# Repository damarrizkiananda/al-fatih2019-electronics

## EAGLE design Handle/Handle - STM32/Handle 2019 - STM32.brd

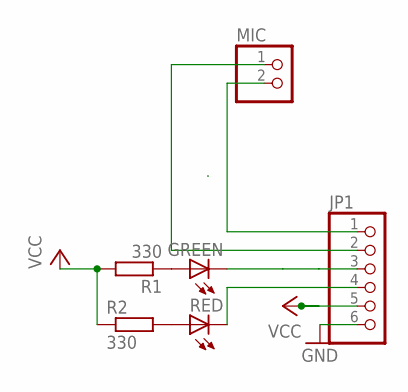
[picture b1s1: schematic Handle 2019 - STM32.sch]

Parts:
GREEN: LED5MM
JP1: PINHD-1X6; 1X06
MIC: PINHD-1X2; 1X02
R1, R2: 330; M1206
RED: LED5MM

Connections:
GND: JP1.6
unnamed: GREEN.K (C), JP1.3
unnamed: JP1.2, MIC.1
unnamed: JP1.1, MIC.2
unnamed: GREEN.A, R1.1
unnamed: R2.2, RED.A
unnamed: JP1.4, RED.K (C)
VCC: JP1.5, R1.2, R2.1

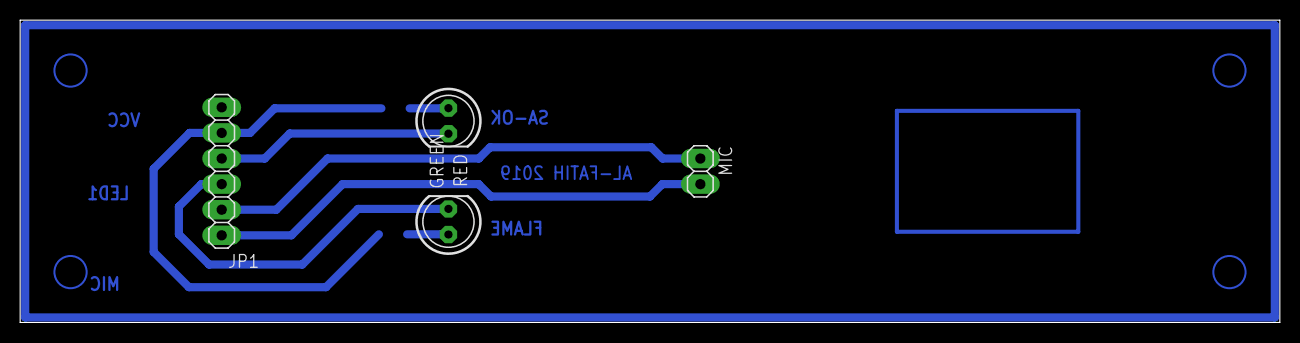
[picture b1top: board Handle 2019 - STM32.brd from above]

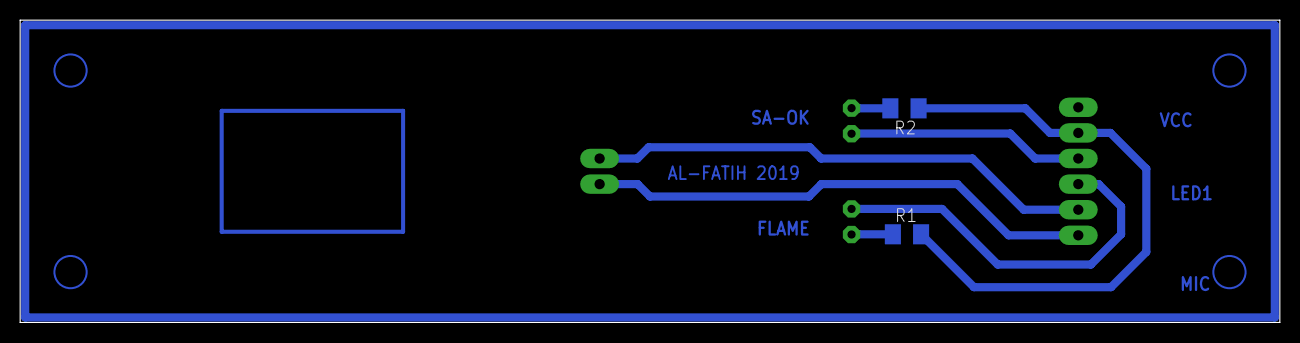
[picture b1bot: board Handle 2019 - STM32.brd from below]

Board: 2 copper layers, 125.0 x 30.0 mm, 6 parts (2 on the bottom side), 7 nets.

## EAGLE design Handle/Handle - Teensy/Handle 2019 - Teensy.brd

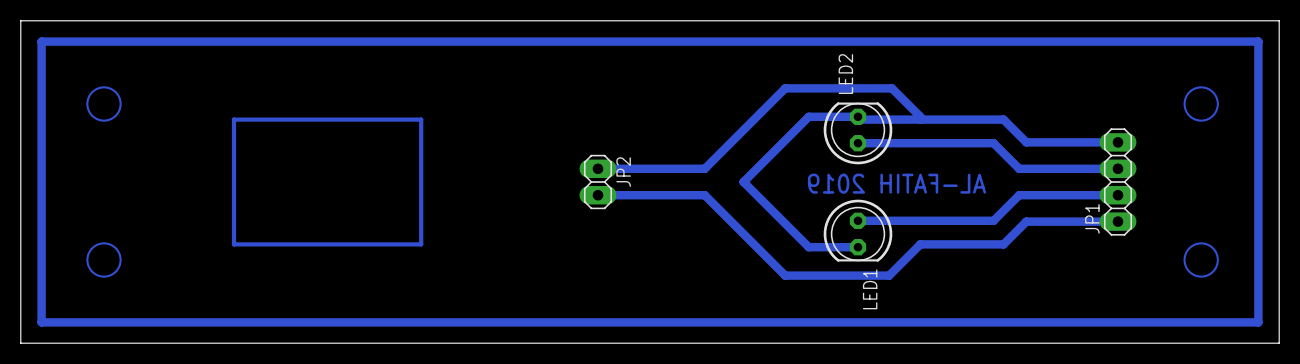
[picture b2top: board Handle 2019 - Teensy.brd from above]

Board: 2 copper layers, 121.0 x 31.0 mm, 4 parts (0 on the bottom side), 4 nets.

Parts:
JP1: 1X04
JP2: 1X02
LED1, LED2: LED5MM

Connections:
GND: JP1.4, JP2.1, LED1.K, LED2.K
LED1: JP1.2, LED1.A
LED2: JP1.3, LED2.A
unnamed: JP1.1, JP2.2

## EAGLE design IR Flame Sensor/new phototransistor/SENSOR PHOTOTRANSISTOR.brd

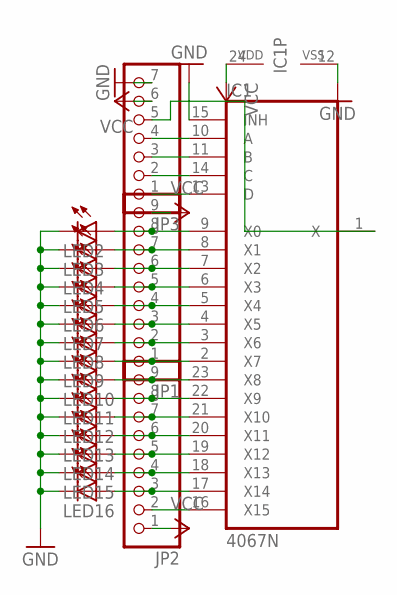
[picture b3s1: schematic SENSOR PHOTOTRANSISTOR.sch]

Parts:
IC1: 4067N; DIL24-6
JP1, JP2: PINHD-1X9; 1X09
JP3: PINHD-1X7; 1X07
LED2, LED3, LED4, LED5, LED6, LED7, LED8, LED9, LED10, LED11, LED12, LED13, LED14, LED15, LED16: LED5MM

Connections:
GND: IC1.12 (VSS), IC1.15 (INH), JP3.7, LED2.K (C), LED3.K (C), LED4.K (C), LED5.K (C), LED6.K (C), LED7.K (C), LED8.K (C), LED9.K (C), LED10.K (C), LED11.K (C), LED12.K (C), LED13.K (C), LED14.K (C), LED15.K (C), LED16.K (C)
unnamed: IC1.9 (X0), JP1.8, LED2.A
unnamed: IC1.8 (X1), JP1.7, LED3.A
unnamed: IC1.7 (X2), JP1.6, LED4.A
unnamed: IC1.6 (X3), JP1.5, LED5.A
unnamed: IC1.5 (X4), JP1.4, LED6.A
unnamed: IC1.4 (X5), JP1.3, LED7.A
unnamed: IC1.3 (X6), JP1.2, LED8.A
unnamed: IC1.2 (X7), JP1.1, LED9.A
unnamed: IC1.23 (X8), JP2.9, LED10.A
unnamed: IC1.22 (X9), JP2.8, LED11.A
unnamed: IC1.21 (X10), JP2.7, LED12.A
unnamed: IC1.20 (X11), JP2.6, LED13.A
unnamed: IC1.19 (X12), JP2.5, LED14.A
unnamed: IC1.18 (X13), JP2.4, LED15.A
unnamed: IC1.17 (X14), JP2.3, LED16.A
unnamed: IC1.16 (X15), JP2.2
unnamed: IC1.13 (D), JP3.1
unnamed: IC1.14 (C), JP3.2
unnamed: IC1.11 (B), JP3.3
unnamed: IC1.10 (A), JP3.4
unnamed: IC1.1 (X), JP3.5
VCC: IC1.24 (VDD), JP1.9, JP2.1, JP3.6

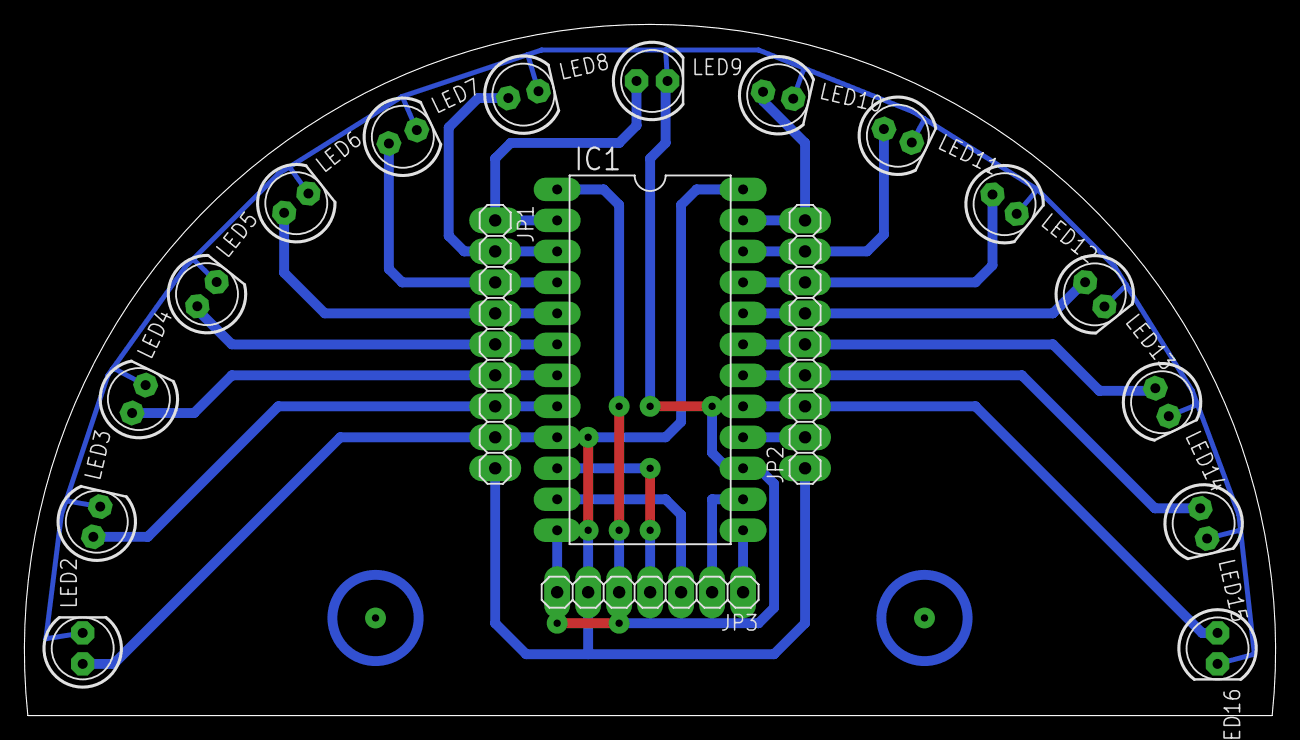
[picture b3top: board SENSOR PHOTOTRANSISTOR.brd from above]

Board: 2 copper layers, 102.6 x 56.7 mm, 19 parts (0 on the bottom side), 23 nets.

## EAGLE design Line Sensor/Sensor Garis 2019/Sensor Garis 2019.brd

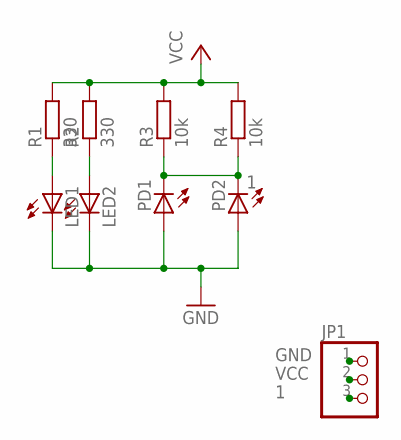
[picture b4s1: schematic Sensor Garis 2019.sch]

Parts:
JP1: PINHD-1X3; 1X03
LED1, LED2: LED3MM
PD1, PD2: LED3MM
R1, R2: 330; M0805
R3, R4: 10k; M0805

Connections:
1: JP1.3, PD1.K (C), PD2.K (C), R3.1, R4.1
GND: JP1.1, LED1.K (C), LED2.K (C), PD1.A, PD2.A
unnamed: LED2.A, R2.1
unnamed: LED1.A, R1.1
VCC: JP1.2, R1.2, R2.2, R3.2, R4.2

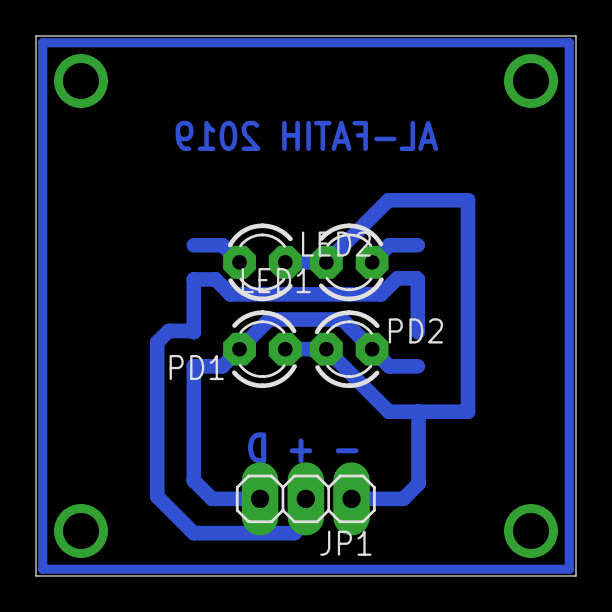
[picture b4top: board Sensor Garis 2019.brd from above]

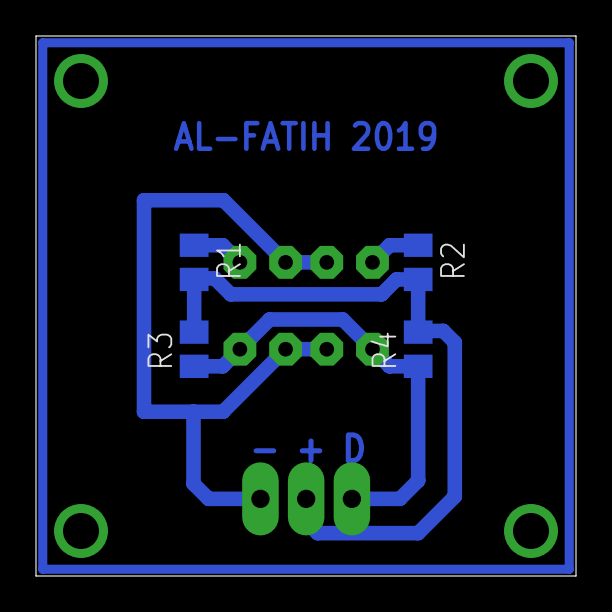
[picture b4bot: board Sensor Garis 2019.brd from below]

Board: 2 copper layers, 30.0 x 30.0 mm, 9 parts (4 on the bottom side), 5 nets.

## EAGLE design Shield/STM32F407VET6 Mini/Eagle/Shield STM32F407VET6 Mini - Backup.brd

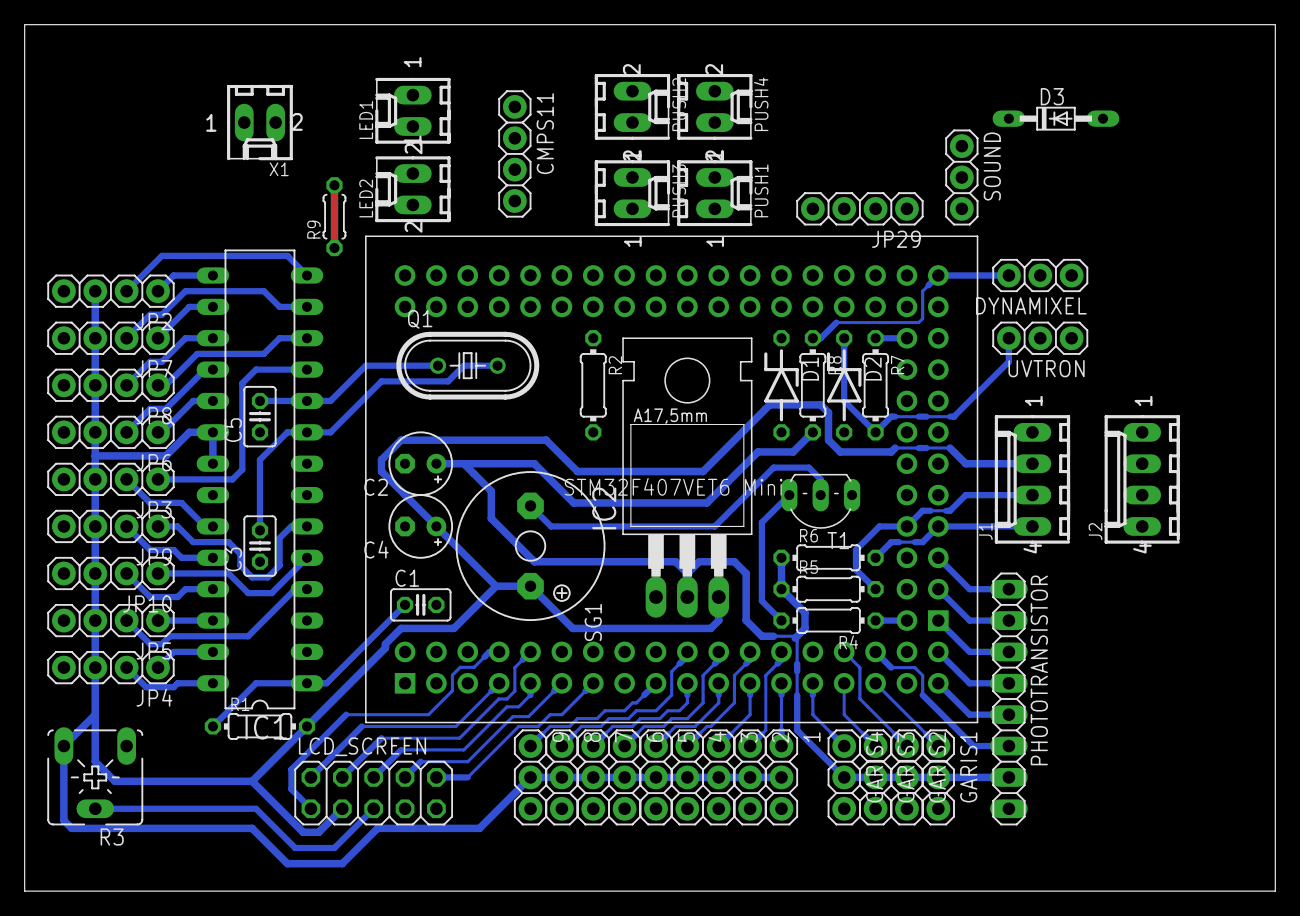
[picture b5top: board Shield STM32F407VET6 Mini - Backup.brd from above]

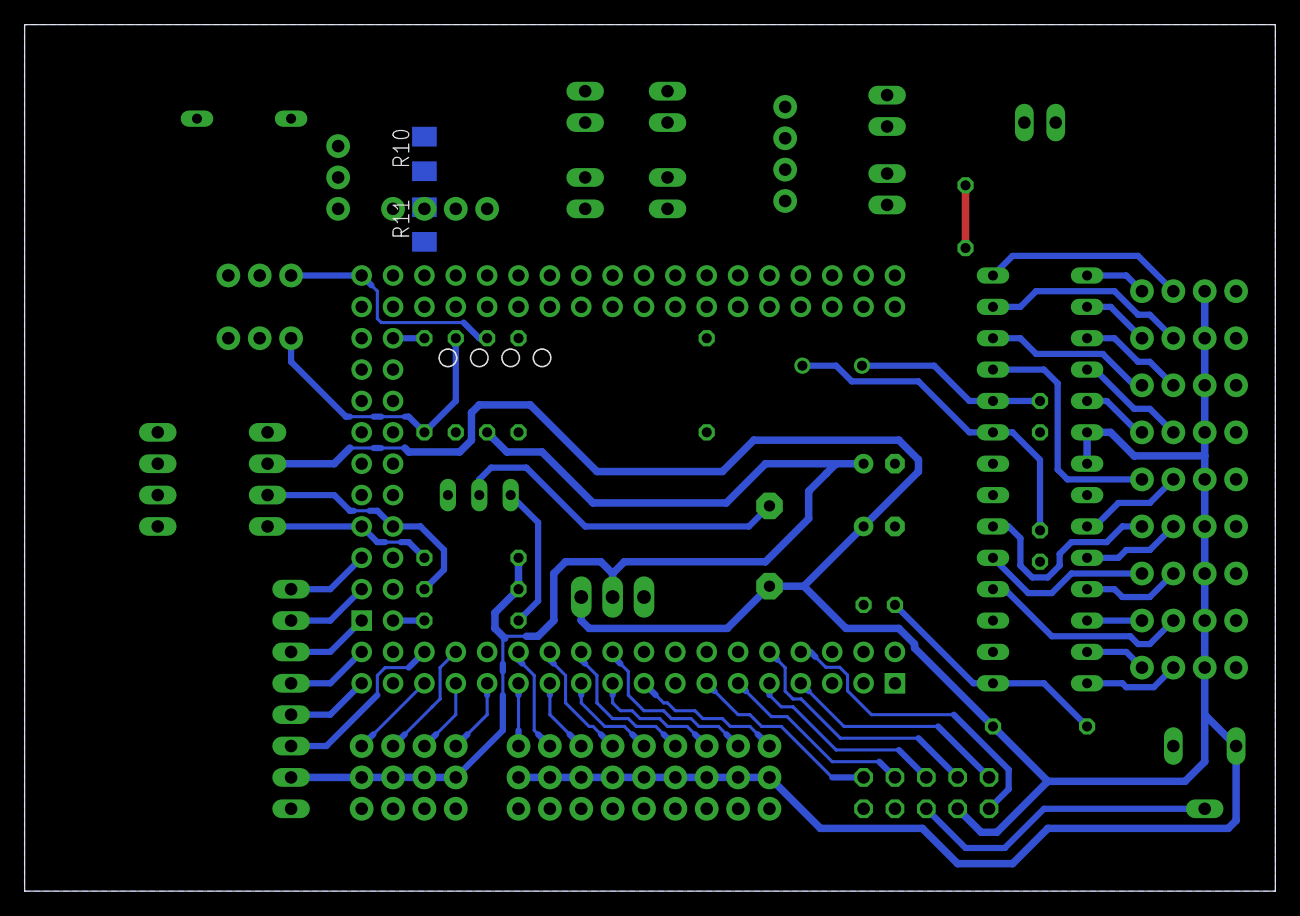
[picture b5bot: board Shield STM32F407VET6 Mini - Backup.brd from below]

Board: 2 copper layers, 101.3 x 70.2 mm, 63 parts (2 on the bottom side), 75 nets.

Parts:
1, 2, 3, 4, 5, 6, 7, 8, 9: 1X03
C1: 1uF; C025-025X050
C2, C4: 10uF Tantalum; E2,5-5
C3, C5: 22 pF; C025-025X050
CMPS11: 1X04
D1, D2: 1N4728; ZDIO-7.5
D3: DO34-7
DYNAMIXEL: 1X03
GARIS1, GARIS2, GARIS3, GARIS4: 1X03
IC1: MEGA8-P; DIL28-3
IC2: LM1117T-3.3; TO220
J1, J2: 22-27-2041-04; 6410-04
JP2, JP3, JP4, JP5, JP6, JP7, JP8, JP9, JP10, JP29: 1X04
LCD_SCREEN: 2X05
LED1, LED2: 22-27-2021-02; 6410-02
PHOTOTRANSISTOR: 1X08
PUSH1, PUSH2, PUSH3, PUSH4: 22-27-2021-02; 6410-02
Q1: 16 Mhz; HC49U70
R1, R8: 10k; 0204/7
R2, R7: 470; 0204/7
R3: 10k; CA6V
R4: 1k; 0204/7
R5, R6: 4k7; 0204/7
R9: 0204/5
R10, R11: 330; M1206
SG1: F/QMBIII
SOUND: 1X03
T1: 2SC945; TO92-ECB
U$2: STM32F407VET6_MINI
UVTRON: 1X03
X1: 22-27-2021-02; 6410-02

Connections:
1: 1.1, U$2.PA4
2: 2.1, U$2.PA5
3: 3.1, U$2.PA1
3.3: C2.+, D3.C, GARIS1.2, GARIS2.2, GARIS3.2, GARIS4.2, IC2.2, LED1.1, LED2.1, PHOTOTRANSISTOR.7, R5.1, R6.1, R8.2
4: 4.1, U$2.PA3
5: 5.1, U$2.PA0
6: 6.1, U$2.PA2
7: 7.1, U$2.PC2
8: 8.1, U$2.PC3
9: 9.1, U$2.PC0
A: PHOTOTRANSISTOR.5, U$2.PE8
B: PHOTOTRANSISTOR.4, U$2.PE9
BZ: R4.1, U$2.PE10
C: PHOTOTRANSISTOR.3, U$2.PE11
D: PHOTOTRANSISTOR.2, U$2.PE13
D4: LCD_SCREEN.4, U$2.PE3
D5: LCD_SCREEN.6, U$2.PE2
D6: LCD_SCREEN.8, U$2.PE4
D7: LCD_SCREEN.10, U$2.PE6
DNX: DYNAMIXEL.3, R8.1, U$2.PC8
E: LCD_SCREEN.2, U$2.PE0
E1: IC1.11, JP3.1
E2: IC1.15, JP2.1
E3: IC1.26, JP5.1
E4: IC1.27, JP4.1
E5: IC1.16, JP7.1
E6: IC1.19, JP6.1
E7: IC1.6, JP9.1
E8: IC1.12, JP8.1
E9: IC1.5, JP10.1
EM: PHOTOTRANSISTOR.1, U$2.PE15
GARIS1: GARIS1.1, U$2.PB0
GARIS2: GARIS2.1, U$2.PC5
GARIS3: GARIS3.1, U$2.PC4
GARIS4: GARIS4.1, U$2.PA6
GND: 1.3, 2.3, 3.3, 4.3, 5.3, 6.3, 7.3, 8.3, 9.3, C1.2, C2.-, C3.1, C4.-, C5.1, CMPS11.1, D1.A, D2.A, DYNAMIXEL.1, GARIS1.3, GARIS2.3, GARIS3.3, GARIS4.3, IC1.8, IC1.22, IC2.1, J1.1, J2.1, JP2.4, JP3.4, JP4.4, JP5.4, JP6.4, JP7.4, JP8.4, JP9.4, JP10.4, JP29.1, LCD_SCREEN.7, LCD_SCREEN.9, PHOTOTRANSISTOR.8, PUSH1.2, PUSH2.2, PUSH3.2, PUSH4.2, R3.A, R9.1, R9.2, SOUND.1, T1.E, U$2.GND, U$2.GND@1, U$2.GND@2, U$2.GND@3, U$2.GND@4, U$2.GND@5, UVTRON.1, X1.2
LED1: R10.1, U$2.PB8
LED2: R11.1, U$2.PB9
unnamed: C1.1, IC1.1, R1.1
unnamed: D3.A, JP29.2
unnamed: C5.2, IC1.10, Q1.1
unnamed: C3.2, IC1.9, Q1.2
unnamed: LED1.2, R10.2
unnamed: D2.C, R7.2, UVTRON.3
unnamed: LCD_SCREEN.5, R3.S
unnamed: LED2.2, R11.2
unnamed: SG1.-, T1.C
unnamed: R4.2, T1.B
unnamed: IC1.3, R2.2
OUTPUT: PHOTOTRANSISTOR.6, U$2.PB1
PUSH1: PUSH1.1, U$2.PD1
PUSH2: PUSH2.1, U$2.PD2
PUSH3: PUSH3.1, U$2.PD3
PUSH4: PUSH4.1, U$2.PD4
RS: LCD_SCREEN.1, U$2.PE1
RX: IC1.2, U$2.PA10
SCL: J1.3, J2.3, R5.2, U$2.PB10
SCL_CMPS11: CMPS11.4, U$2.PB6
SDA: J1.4, J2.4, R6.2, U$2.PB11
SDA_CMPS11: CMPS11.3, U$2.PB7
SOUND: SOUND.3, U$2.PC9
SWCLK: JP29.3, U$2.PA14
SWDIO: JP29.4, U$2.PA13
T1: IC1.23, JP3.2
T2: IC1.14, JP2.2
T3: IC1.4, JP5.2
T4: IC1.28, JP4.2
T5: IC1.13, JP7.2
T6: IC1.18, JP6.2
T7: IC1.24, JP9.2
T8: IC1.17, JP8.2
T9: IC1.25, JP10.2
TX: D1.C, R2.1, U$2.PA9
UV: R7.1, U$2.PD14
VCC: 1.2, 2.2, 3.2, 4.2, 5.2, 6.2, 7.2, 8.2, 9.2, C4.+, CMPS11.2, DYNAMIXEL.2, IC1.7, IC1.20, IC1.21, IC2.3, J1.2, J2.2, JP2.3, JP3.3, JP4.3, JP5.3, JP6.3, JP7.3, JP8.3, JP9.3, JP10.3, LCD_SCREEN.3, R1.2, R3.E, SG1.+, SOUND.2, UVTRON.2, X1.1

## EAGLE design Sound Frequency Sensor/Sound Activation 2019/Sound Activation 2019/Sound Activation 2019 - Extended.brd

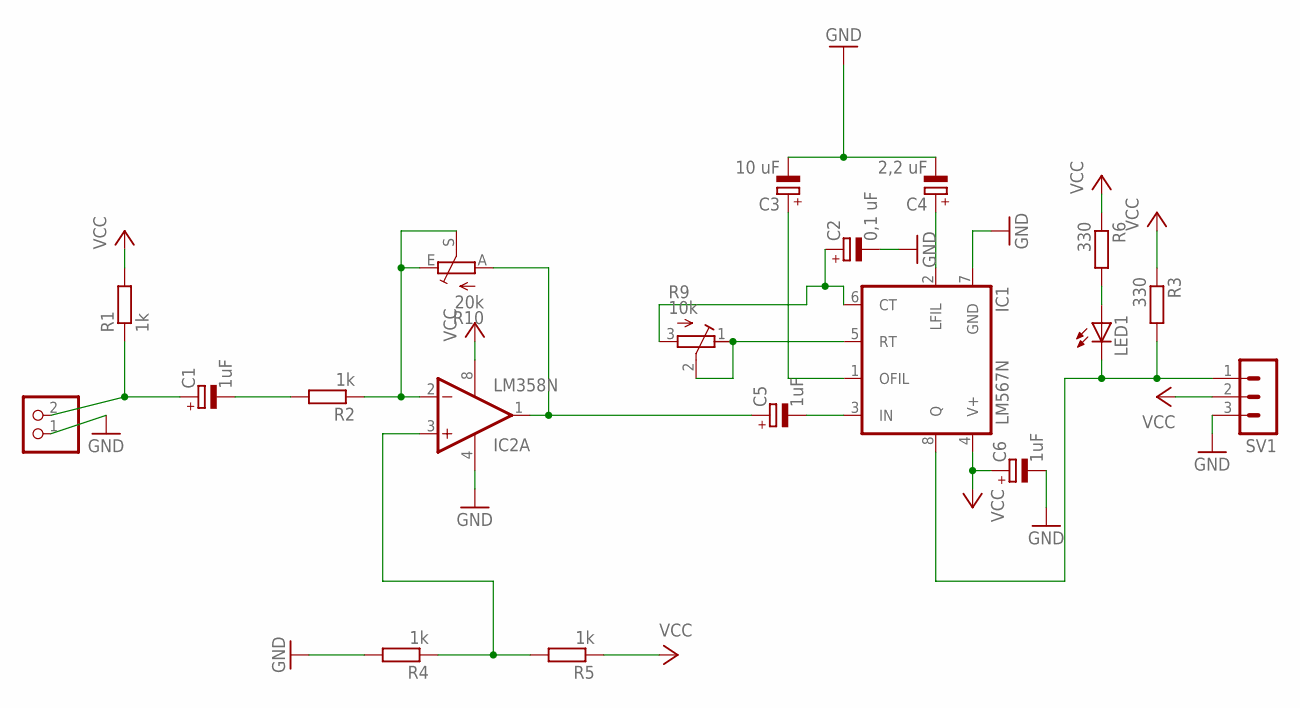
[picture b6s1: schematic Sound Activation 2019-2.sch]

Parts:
C1, C5, C6: 1uF; E1,8-4
C2: 0,1 uF; E1,8-4
C3: 10 uF; E1,8-4
C4: 2,2 uF; E1,8-4
IC1: LM567N; DIL08
IC2: LM358N; DIL08
LED1: LED3MM
M1: PINHD-1X2; 1X02
R1, R2, R4, R5: 1k; 0204/7
R3, R6: 330; 0204/7
R9: 10k; RTRIM3006P
R10: 20k; B25P
SV1: MA03-1

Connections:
GND: C2.-, C3.-, C4.-, C6.-, IC1.7 (GND), IC2.4 (V-), M1.1, R4.2, SV1.3
unnamed: IC2.2 (-IN), R2.1, R10.E, R10.S
unnamed: IC2.3 (+IN), R4.1, R5.2
unnamed: C1.+, M1.2, R1.1
unnamed: C1.-, R2.2
unnamed: C2.+, IC1.6 (CT), R9.3 (A)
unnamed: IC1.5 (RT), R9.1 (E), R9.2 (S)
unnamed: C5.+, IC2.1 (OUT), R10.A
unnamed: IC1.8 (Q), LED1.K (C), R3.2, SV1.1
unnamed: LED1.A, R6.2
unnamed: C5.-, IC1.3 (IN)
unnamed: C3.+, IC1.1 (OFIL)
unnamed: C4.+, IC1.2 (LFIL)
VCC: C6.+, IC1.4 (V+), IC2.8 (V+), R1.2, R3.1, R5.1, R6.1, SV1.2

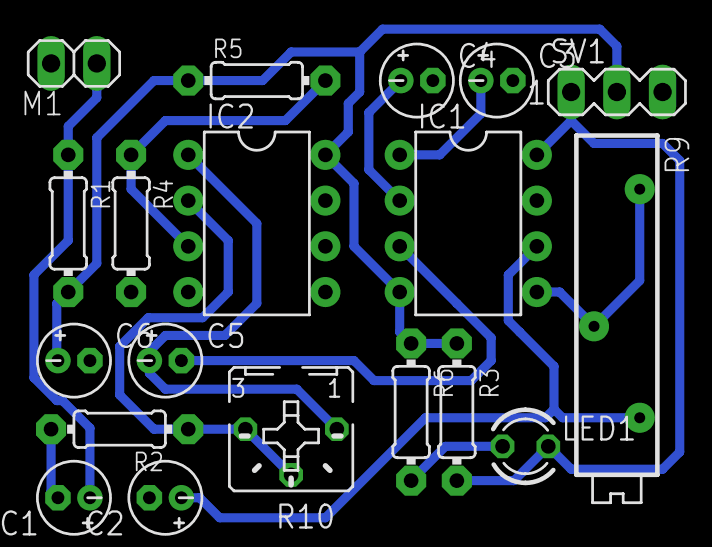
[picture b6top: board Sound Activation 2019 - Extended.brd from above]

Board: 2 copper layers, 19 parts (0 on the bottom side), 14 nets.
